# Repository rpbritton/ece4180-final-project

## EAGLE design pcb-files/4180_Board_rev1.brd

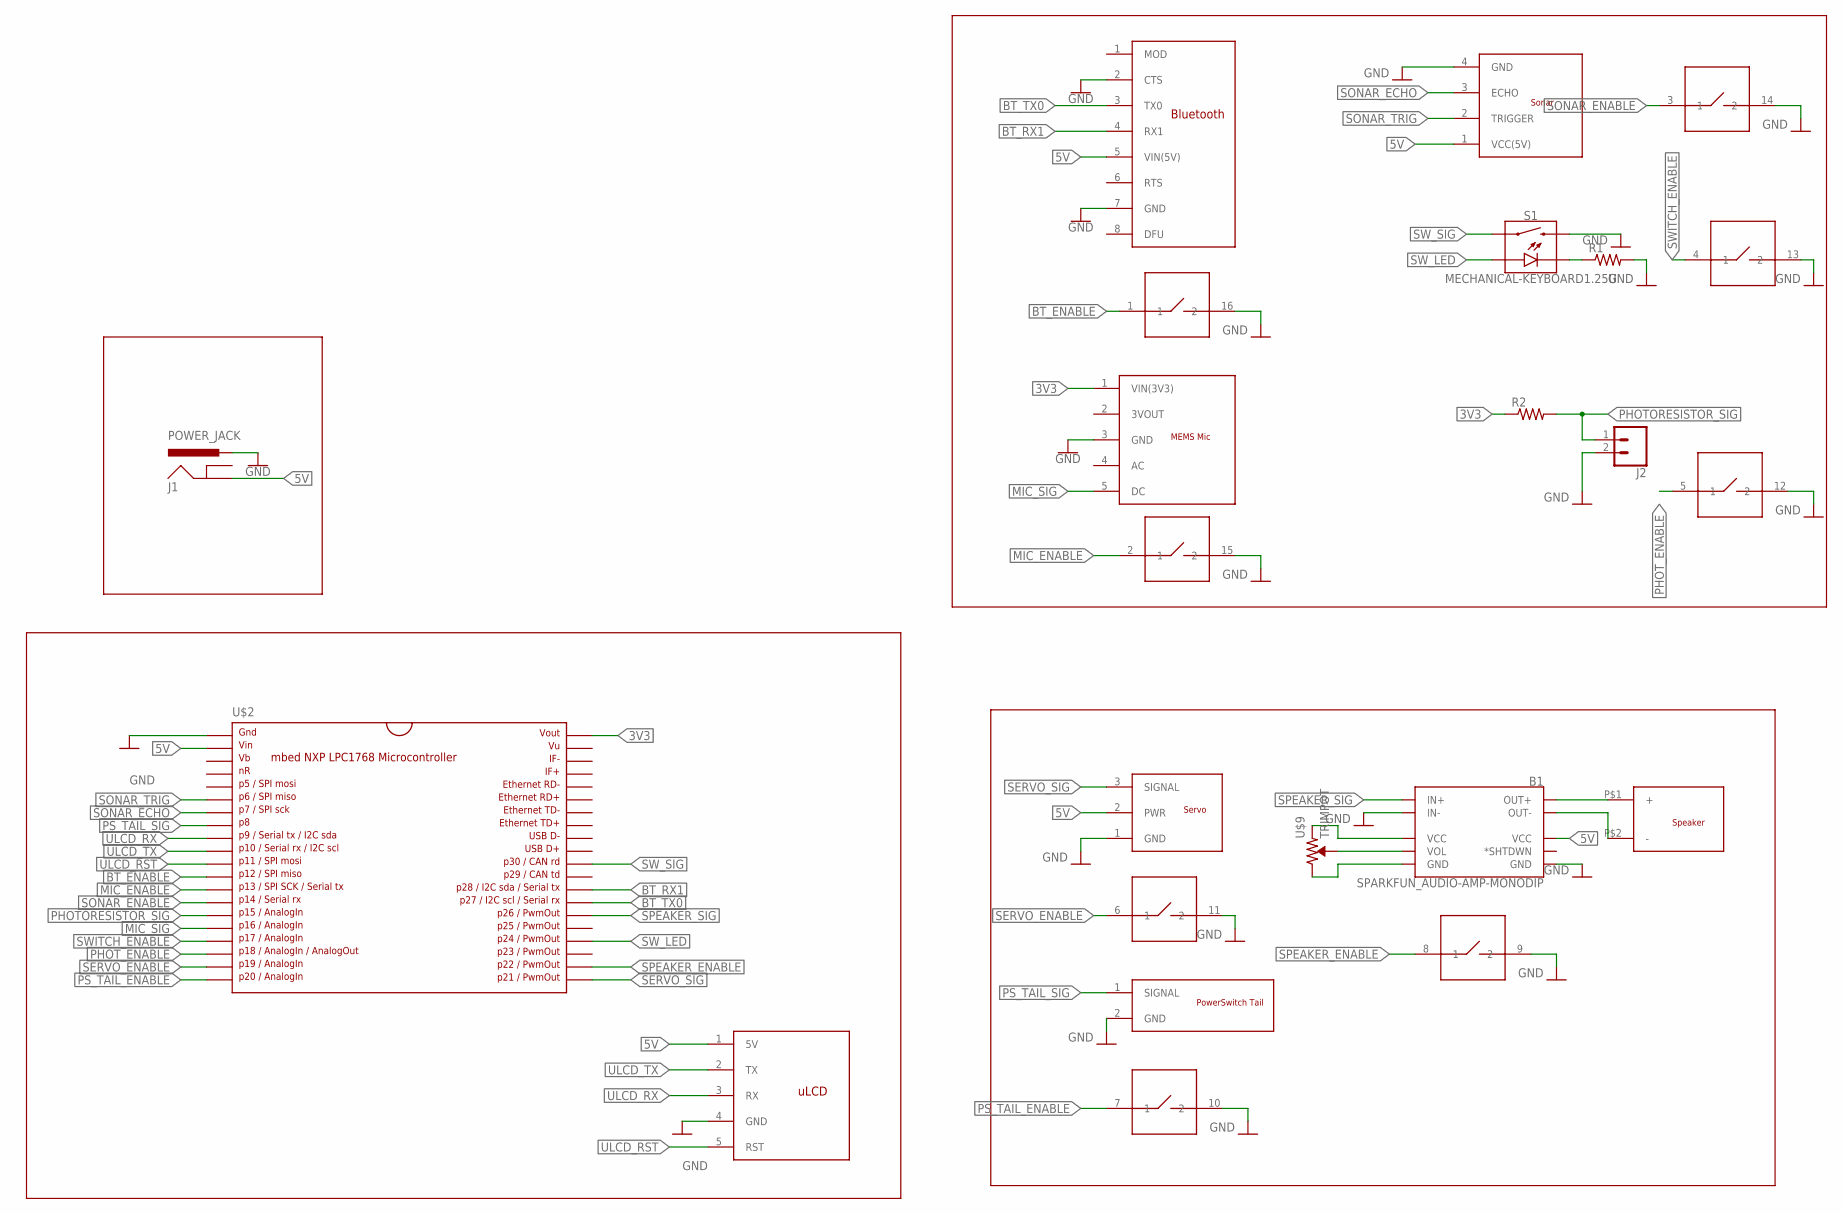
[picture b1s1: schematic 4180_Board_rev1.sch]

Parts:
B1: SPARKFUN_AUDIO-AMP-MONODIP; AUDIO-AMP-MONO
J1: POWER_JACK; POWER_JACK_PTH
J2: CONN_02; 1X02
R1, R2: ADAFRUIT_R-US_0309/12; ADAFRUIT_0309/12
S1: MECHANICAL-KEYBOARD1.25U; CHERRY-MX-LED-1.25U
U$1: BLUETOOTH; 1X08
U$2: MBED1768; DIL40_0.9
U$3: MEMS_MIC; 1X05
U$4: POWERSWITCHTAIL; 1X02
U$5: SERVO; 1X03
U$6: SONAR; 1X04
U$7: SPEAKER
U$8: ULCD; 1X05
U$9: TRIMPOT
U$10: DIP_SWITCH_8; DIP16

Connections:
3V3: R2.1, U$2.40, U$3.1 (VIN(3V3))
5V: B1.PWR+ (VCC), J1.PWR (GND), U$1.5 (VIN(5V)), U$2.2, U$5.2 (PWR), U$6.1 (VCC(5V)), U$8.1 (5V)
BT_ENABLE: U$2.12, U$10.1
BT_RX1: U$1.4 (RX1), U$2.28
BT_TX0: U$1.3 (TX0), U$2.27
GND: B1.IN-, B1.PWR- (GND), J1.GND (PWR), J2.2, R1.2, S1.S2 (2), U$1.2 (CTS), U$1.7 (GND), U$2.1, U$3.3 (GND), U$4.2 (GND), U$5.1 (GND), U$6.4 (GND), U$8.4 (GND), U$10.9 (2), U$10.10 (2), U$10.11 (2), U$10.12 (2), U$10.13 (2), U$10.14 (2), U$10.15 (2), U$10.16 (2)
MIC_ENABLE: U$2.13, U$10.2 (1)
MIC_SIG: U$2.16, U$3.5 (DC)
unnamed: R1.1, S1.K (C)
unnamed: B1.VOL+ (VCC), U$9.P$1 (CCW)
unnamed: B1.VOL, U$9.P$3 (WIPER)
unnamed: B1.VOL- (GND), U$9.P$2 (CW)
unnamed: B1.OUT+, U$7.P$1 (+)
unnamed: B1.OUT-, U$7.P$2 (-)
PHOTORESISTOR_SIG: J2.1, R2.2, U$2.15
PHOT_ENABLE: U$2.18, U$10.5 (1)
PS_TAIL_ENABLE: U$2.20, U$10.7 (1)
PS_TAIL_SIG: U$2.8, U$4.1 (SIGNAL)
SERVO_ENABLE: U$2.19, U$10.6 (1)
SERVO_SIG: U$2.21, U$5.3 (SIGNAL)
SONAR_ECHO: U$2.7, U$6.3 (ECHO)
SONAR_ENABLE: U$2.14, U$10.3 (1)
SONAR_TRIG: U$2.6, U$6.2 (TRIGGER)
SPEAKER_ENABLE: U$2.22, U$10.8 (1)
SPEAKER_SIG: B1.IN+, U$2.26
SWITCH_ENABLE: U$2.17, U$10.4 (1)
SW_LED: S1.A, U$2.24
SW_SIG: S1.S1 (1), U$2.30
ULCD_RST: U$2.11, U$8.5 (RST)
ULCD_RX: U$2.9, U$8.3 (RX)
ULCD_TX: U$2.10, U$8.2 (TX)

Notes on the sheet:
Bluetooth

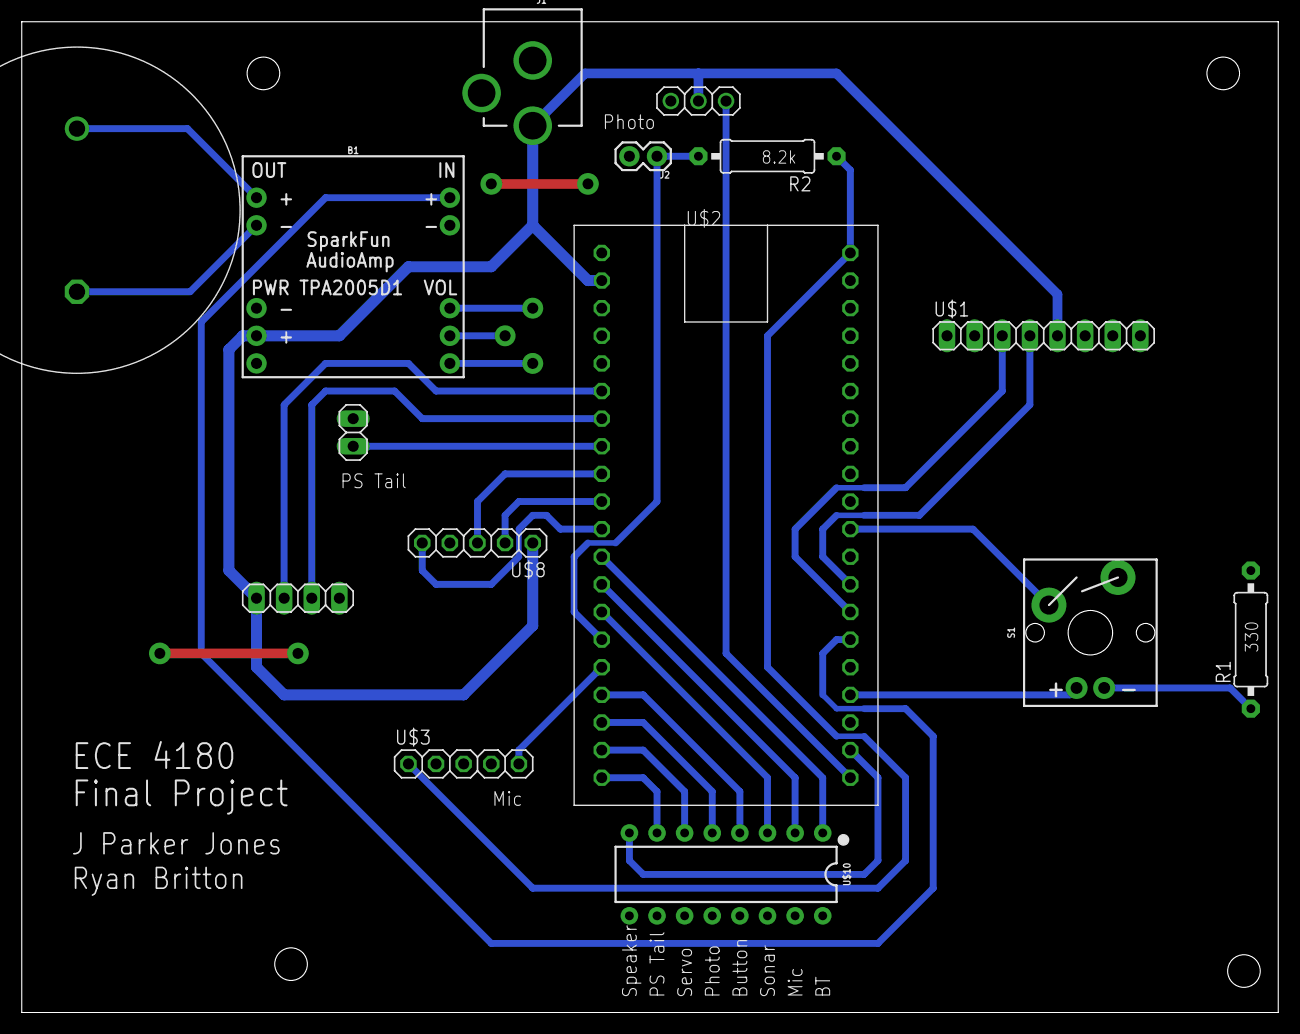
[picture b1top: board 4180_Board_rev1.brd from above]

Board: 2 copper layers, 115.5 x 91.1 mm, 16 parts (0 on the bottom side), 31 nets.

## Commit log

2022-04-07 Initial blinky commit
2022-04-07 Add quick little button activator
2022-04-07 Add PinDetect library
2022-04-08 Add bluetooth activator
2022-04-08 Add include guards
2022-04-10 Added light sensor and sonar. Modified main to test
2022-04-11 Add clapper using rtos sampling
2022-04-11 Add output class
2022-04-17 Added Servo and Speaker Output control
2022-04-18 Add missing enable functions to activators
2022-04-18 Add outlet output
2022-04-18 Update outlet logic to not change when disabled
2022-04-18 Add lcd module class, not fully linked in main
2022-04-18 Fix various broken merges
2022-04-18 Update main and fix polymorphism virtual functions
2022-04-18 Consolidate output enable/activate code
2022-04-18 Consolidate activator enabling
2022-04-18 Expose clapper threshold
2022-04-18 Don't track pointers in LCD
2022-04-18 Run autoformatter
2022-04-18 Center states on LCD
2022-04-20 Don't mark disabled outputs as active
2022-04-20 Add dipswitch implementation
2022-04-20 Remove pointers to hardware, store instead in classes
2022-04-20 Invert dipswitch
2022-04-28 Add pcb files

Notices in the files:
parts and their libraries:
SparkFun-Connectors: Licensing: Creative Commons ShareAlike 4.0 International - https://creativecommons.org/licenses/by-sa/4.0
